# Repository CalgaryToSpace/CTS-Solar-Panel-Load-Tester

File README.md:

# CTS-Solar-Panel-Load-Tester
A solar cell/panel testing device which places a variable load on a panel to characterize its IV/PV curve

## Description

An Arduino controls a MOSFET, acting as a resistor load, to allow varying current through the MOSFET from the solar panels. Two measures are used to monitor current - an INA219 current sensor, and a shunt resistor with an op-amp network. An ADC measures the total cell/panel voltage.

The Arduino logs the voltage/current values over UART to a computer.

## Notes

* R_shunt = Full Scale Voltage / Max Expected Load Current =  40mV / 0.5A = 80mOhms, so 0.1 ohms is reasonable

## License

The software is licensed under [The Unlicense](https://choosealicense.com/licenses/unlicense/). The hardware is licensed under the [CERN Open Hardware Licence Version 2 - Permissive](https://choosealicense.com/licenses/cern-ohl-p-2.0/).

Please see the respective license documents in each sub-folder.

## Similar Projects

* **Main Reference:** https://circuitdigest.com/microcontroller-projects/adustable-electronic-dc-load-using-arduino

* https://jasper.sikken.nl/electronicload/index.html
    * Uses an [IRLZ44Z MOSFET](https://www.infineon.com/dgdl/irlz44zpbf.pdf?fileId=5546d462533600a4015356722836272a)
    * Archived on [the Wayback Machine](https://web.archive.org/web/20240229184606/https://jasper.sikken.nl/electronicload/index.html)
    
## Future Changes

* **Detect cracks in cells:** Add a MOSFET to briefly pulse a voltage across the cells and trigger an infrared camera to take a photo.

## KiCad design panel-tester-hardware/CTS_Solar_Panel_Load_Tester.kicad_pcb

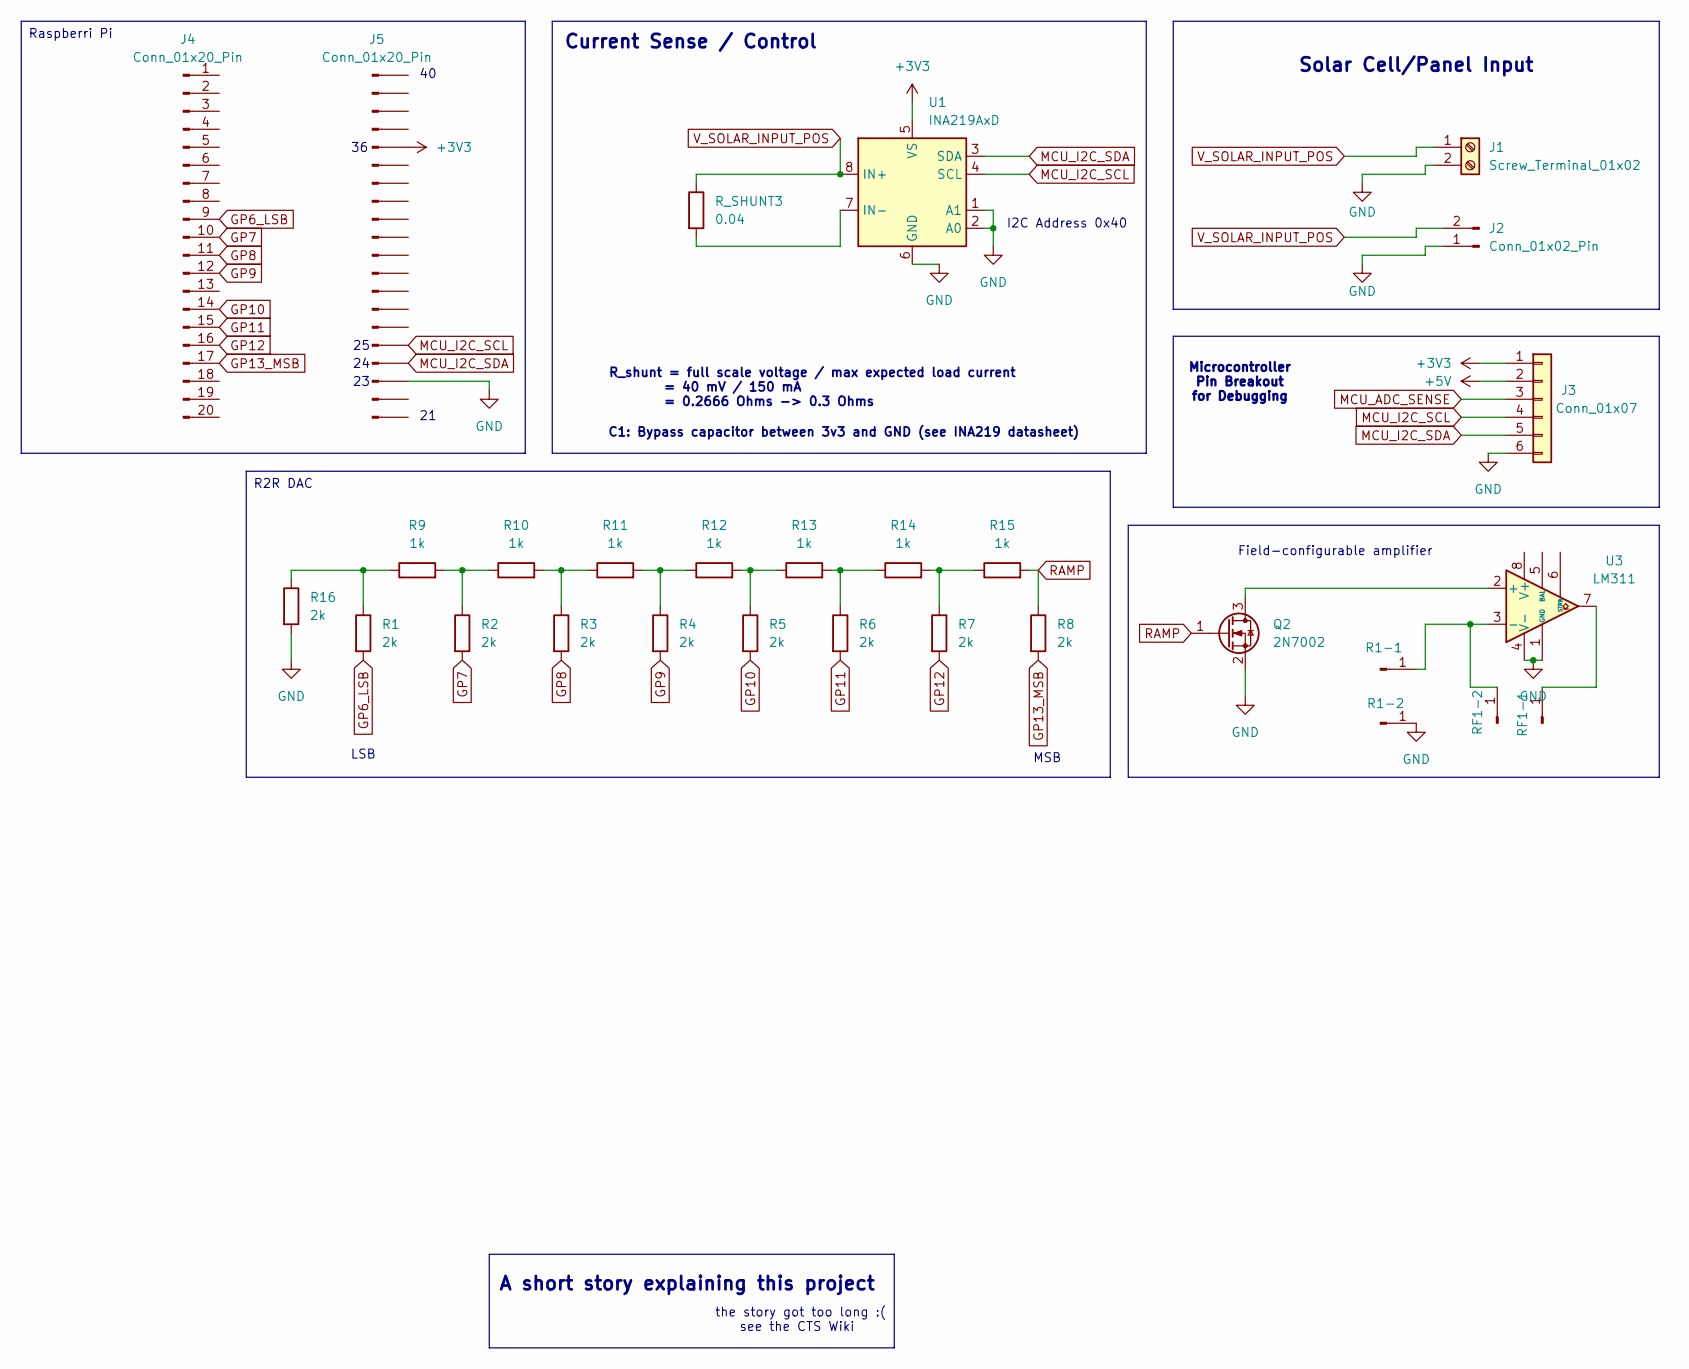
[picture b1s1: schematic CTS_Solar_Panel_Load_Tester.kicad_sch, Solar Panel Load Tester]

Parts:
J1: Screw_Terminal_01x02; TerminalBlock_bornier-2_P5.08mm
J2: Conn_01x02_Pin; PinHeader_1x02_P2.54mm_Vertical
J3: Conn_01x07; PinHeader_1x06_P2.54mm_Vertical
J4, J5: Conn_01x20_Pin; PinHeader_1x20_P2.54mm_Vertical
Q2: 2N7002; SOT-23
R1, R2, R3, R4, R5, R6, R7, R8, R16: 2k; R_1206_3216Metric_Pad1.30x1.75mm_HandSolder
R1-1, R1-2: PinHeader_1x01_P2.54mm_Vertical
R9, R10, R11, R12, R13, R14, R15: 1k; R_1206_3216Metric_Pad1.30x1.75mm_HandSolder
RF1-1, RF1-2: PinHeader_1x01_P2.54mm_Vertical
R_SHUNT3: 0.04; R_2512_6332Metric_Pad1.40x3.35mm_HandSolder
U1: INA219AxD; SOIC-8_3.9x4.9mm_P1.27mm
U3: LM311; SOIC-8-1EP_3.9x4.9mm_P1.27mm_EP2.95x4.9mm_Mask2.71x3.4mm

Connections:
+3V3: J3.1, J5.5, U1.5 (VS)
+5V: J3.2
GND: J1.2, J2.1, J3.6, J5.18, Q2.2 (S), R1-2.1, R16.2, U1.1 (A1), U1.2 (A0), U1.6 (GND), U3.1 (GND), U3.4 (V-)
GP6_LSB: J4.9, R1.2
GP7: J4.10, R2.2
GP8: J4.11, R3.2
GP9: J4.12, R4.2
GP10: J4.14, R5.2
GP11: J4.15, R6.2
GP12: J4.16, R7.2
GP13_MSB: J4.17, R8.2
MCU_ADC_SENSE: J3.3
MCU_I2C_SCL: J3.4, J5.16, U1.4 (SCL)
MCU_I2C_SDA: J3.5, J5.17, U1.3 (SDA)
unnamed: Q2.3 (D), U3.2 (+)
unnamed: R1-1.1, RF1-2.1, U3.3 (-)
unnamed: R1.1, R9.1, R16.1
unnamed: R2.1, R9.2, R10.1
unnamed: R3.1, R10.2, R11.1
unnamed: R4.1, R11.2, R12.1
unnamed: R5.1, R12.2, R13.1
unnamed: R6.1, R13.2, R14.1
unnamed: R7.1, R14.2, R15.1
unnamed: RF1-1.1, U3.7
unnamed: R_SHUNT3.2, U1.7 (IN-)
RAMP: Q2.1 (G), R8.1, R15.2
V_SOLAR_INPUT_POS: J1.1, J2.2, R_SHUNT3.1, U1.8 (IN+)

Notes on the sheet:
Current Sense / Control
Solar Cell/Panel Input
C1: Bypass capacitor between 3v3 and GND (see INA219 datasheet)
R_shunt = full scale voltage / max expected load current = 40 mV / 150 mA = 0.2666 Ohms -> 0.3 Ohms
Field-configurable amplifier
I2C Address 0x40
Microcontroller Pin Breakout for Debugging
LSB
the story got too long :( see the CTS Wiki
A short story explaining this project
MSB
R2R DAC
Raspberri Pi

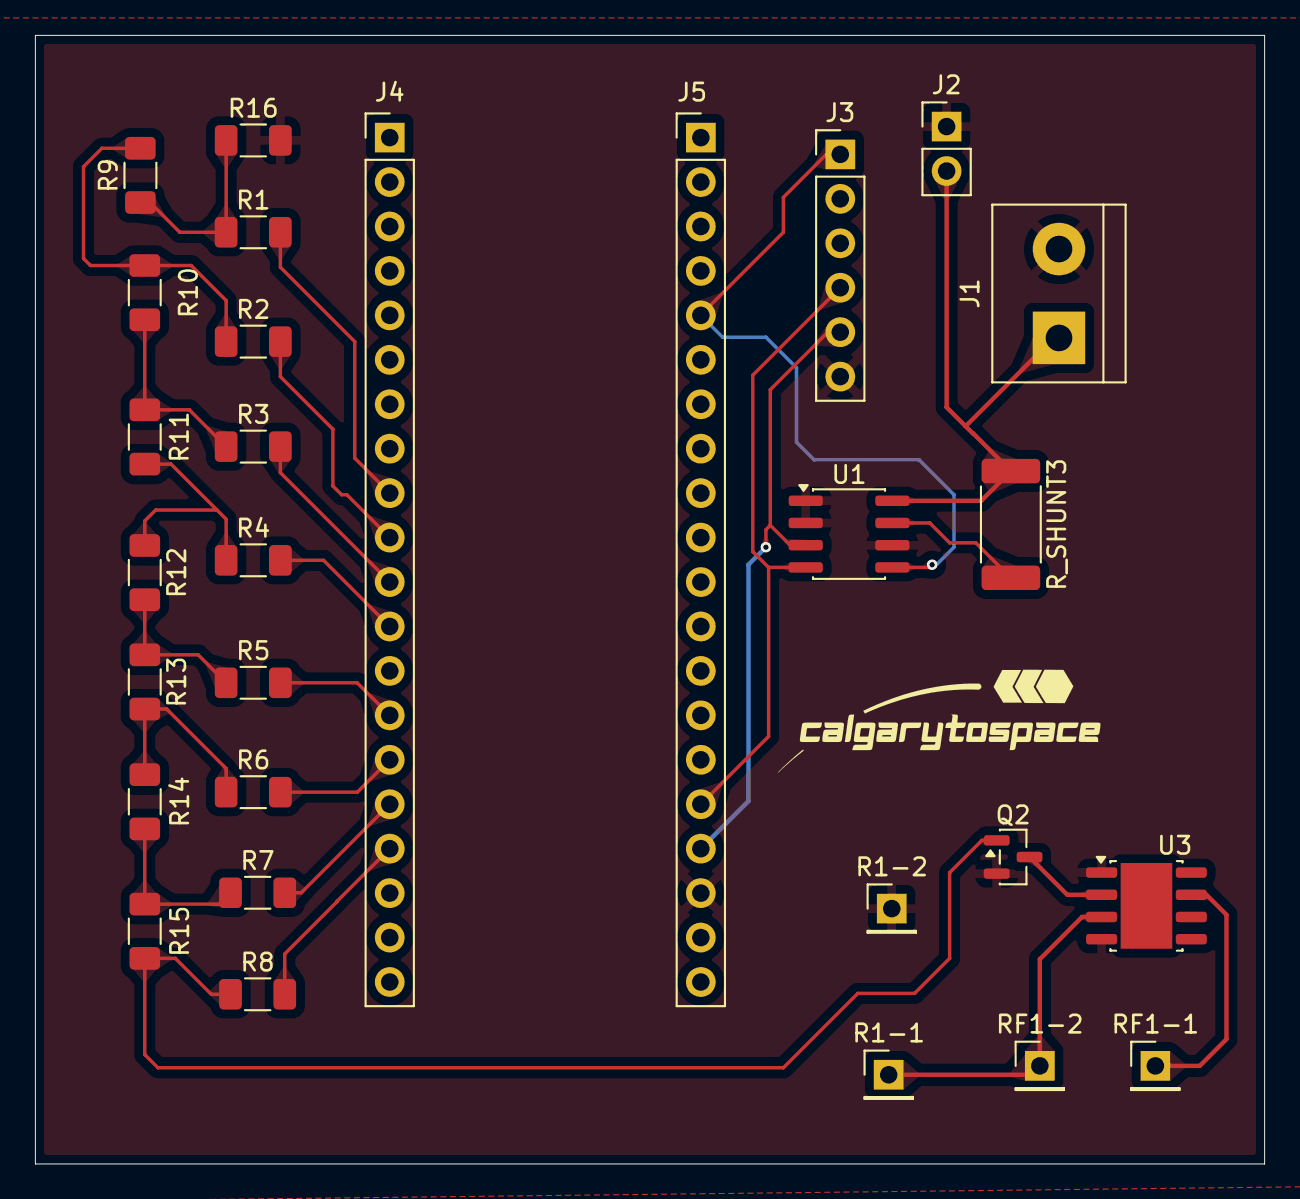
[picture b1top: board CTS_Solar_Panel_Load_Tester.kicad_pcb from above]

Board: 2 copper layers, 70.2 x 64.5 mm, 29 parts (0 on the bottom side), 25 nets.

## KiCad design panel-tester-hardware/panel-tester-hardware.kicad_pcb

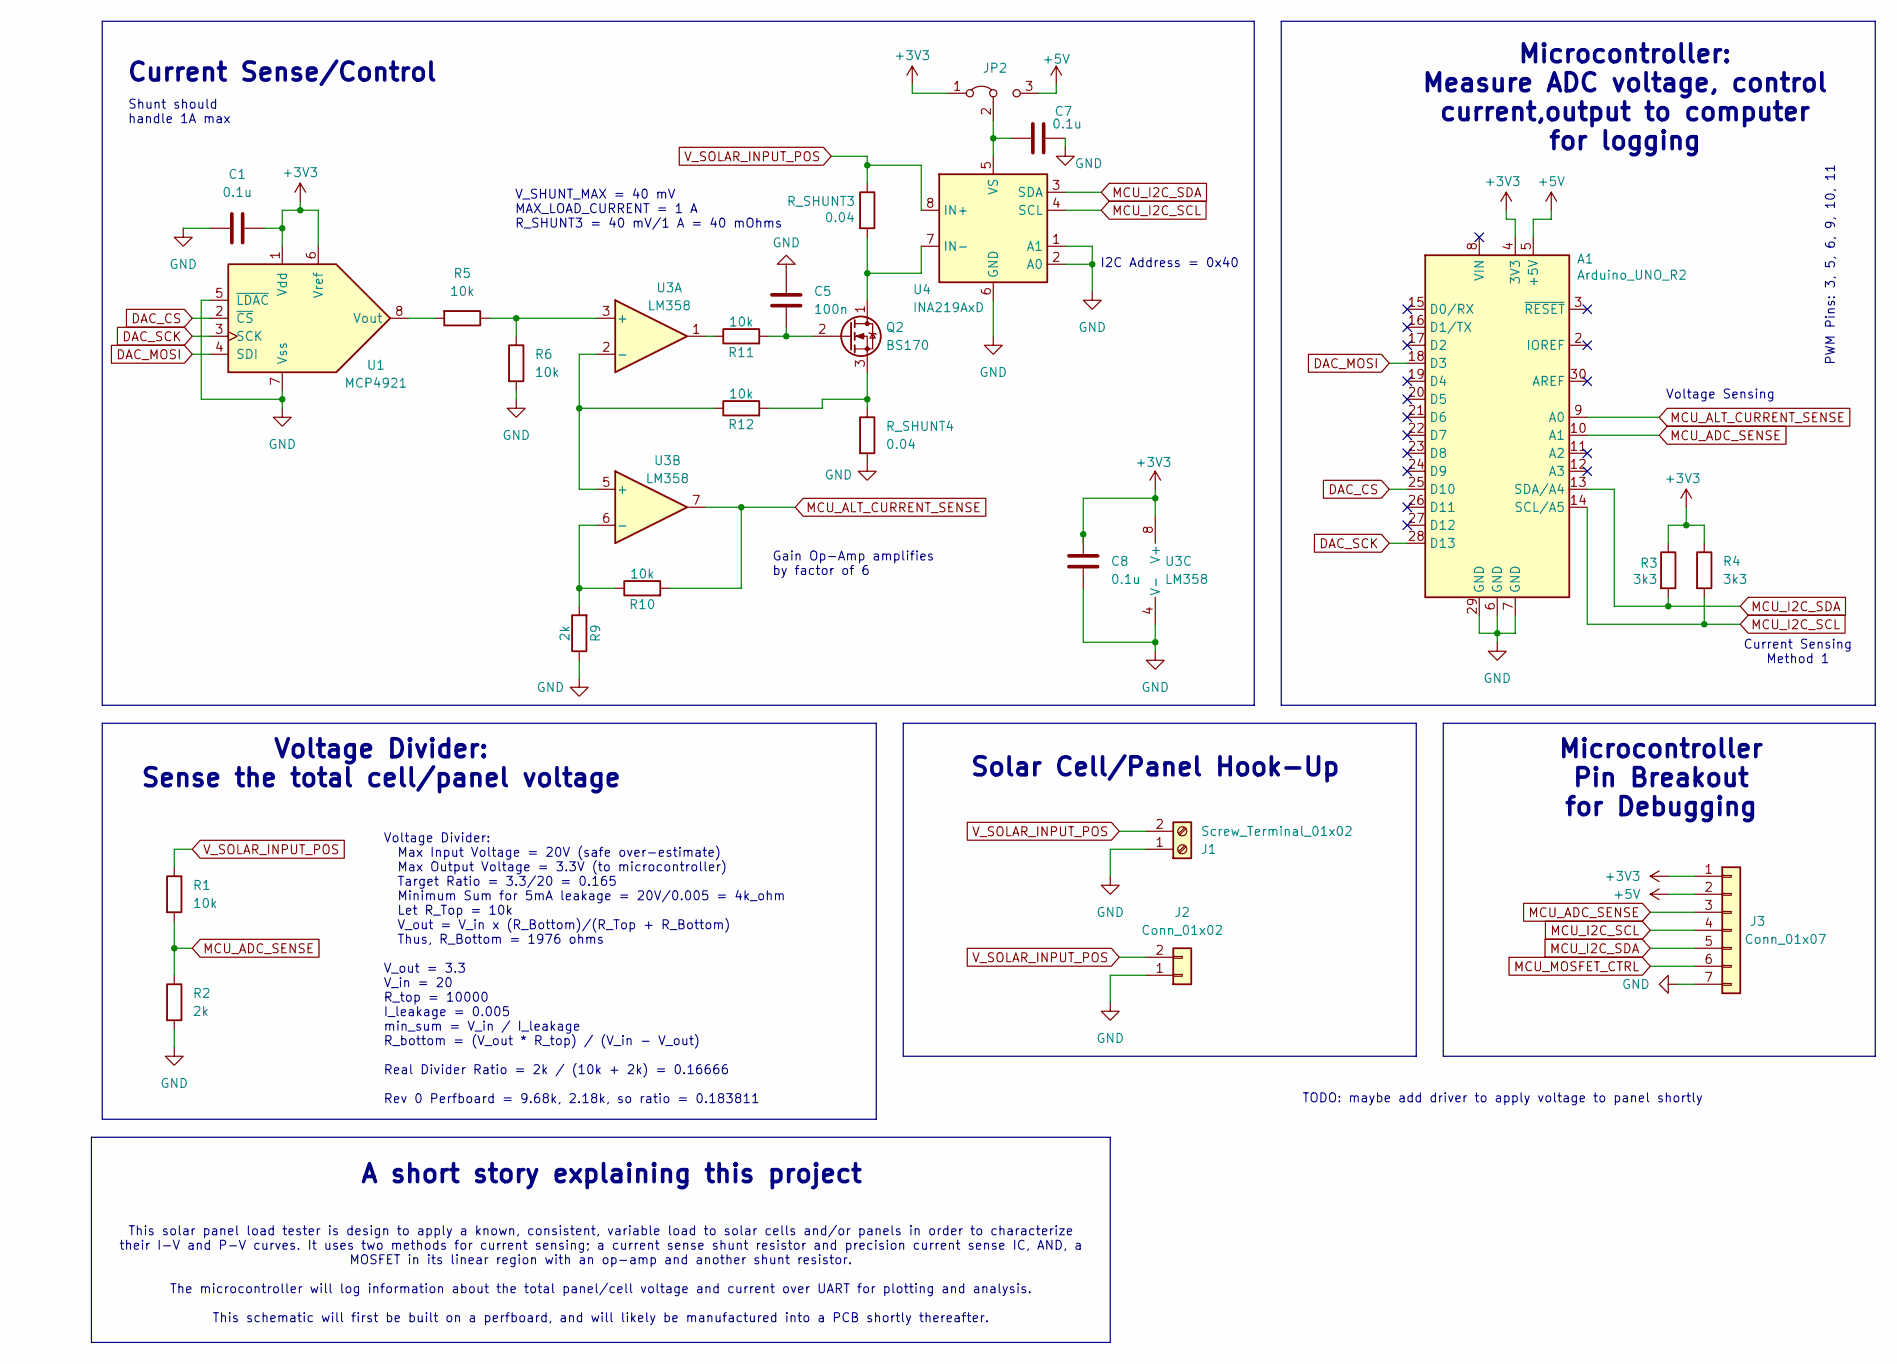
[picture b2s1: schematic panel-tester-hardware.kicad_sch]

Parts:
A1: Arduino_UNO_R2
C1, C7, C8: 0.1u; C_1206_3216Metric_Pad1.33x1.80mm_HandSolder
C5: 100n; C_1206_3216Metric_Pad1.33x1.80mm_HandSolder
J1: Screw_Terminal_01x02; TerminalBlock_bornier-2_P5.08mm
J2: Conn_01x02; PinHeader_1x02_P2.54mm_Vertical
J3: Conn_01x07; PinHeader_1x07_P2.54mm_Vertical
JP2: Jumper_3_Bridged12; SolderJumper-3_P1.3mm_Open_RoundedPad1.0x1.5mm_NumberLabels
Q2: BS170; TO-220-3_Vertical
R1, R5, R6, R10, R11, R12: 10k; R_1206_3216Metric_Pad1.30x1.75mm_HandSolder
R2, R9: 2k; R_1206_3216Metric_Pad1.30x1.75mm_HandSolder
R3, R4: 3k3; R_1206_3216Metric_Pad1.30x1.75mm_HandSolder
R_SHUNT3, R_SHUNT4: 0.04; R_2512_6332Metric_Pad1.40x3.35mm_HandSolder; LCSC C2904248
U1: MCP4921; SOIC-8_3.9x4.9mm_P1.27mm; LCSC C43499
U3: LM358; DIP-8_W7.62mm_LongPads; LCSC C18164495
U4: INA219AxD; SOIC-8_3.9x4.9mm_P1.27mm; LCSC C2155799

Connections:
+3V3: A1.4 (3V3), C1.2, C8.1, J3.1, JP2.1 (A), R3.1, R4.1, U1.1 (Vdd), U1.6 (Vref), U3.8 (V+)
+5V: A1.5 (+5V), J3.2, JP2.3 (B)
DAC_CS: A1.25 (D10), U1.2 (~CS)
DAC_MOSI: A1.18 (D3), U1.4 (SDI)
DAC_SCK: A1.28 (D13), U1.3 (SCK)
GND: A1.6 (GND), A1.7 (GND), A1.29 (GND), C1.1, C5.1, C7.2, C8.2, J1.1, J2.1, J3.7, R2.2, R6.2, R9.1, R_SHUNT4.2, U1.5 (~LDAC), U1.7 (Vss), U3.4 (V-), U4.1 (A1), U4.2 (A0), U4.6 (GND)
MCU_ADC_SENSE: A1.10 (A1), J3.3, R1.2, R2.1
MCU_ALT_CURRENT_SENSE: A1.9 (A0), R10.2, U3.7
MCU_I2C_SCL: A1.14 (SCL/A5), J3.4, R4.2, U4.4 (SCL)
MCU_I2C_SDA: A1.13 (SDA/A4), J3.5, R3.2, U4.3 (SDA)
unnamed: C7.1, JP2.2 (C), U4.5 (VS)
unnamed: Q2.1 (D), R_SHUNT3.2, U4.7 (IN-)
unnamed: C5.2, Q2.2 (G), R11.2
unnamed: Q2.3 (S), R12.2, R_SHUNT4.1
unnamed: R11.1, U3.1
unnamed: R5.1, R6.1, U3.3 (+)
unnamed: R12.1, U3.2 (-), U3.5 (+)
unnamed: R9.2, R10.1, U3.6 (-)
V_SOLAR_INPUT_POS: J1.2, J2.2, R1.1, R_SHUNT3.1, U4.8 (IN+)

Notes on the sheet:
A short story explaining this project
I2C Address = 0x40
Microcontroller Pin Breakout for Debugging
Current Sense/Control
Current Sensing Method 1
TODO: maybe add driver to apply voltage to panel shortly
Microcontroller: Measure ADC voltage, control current,output to computer for logging
Voltage Divider: Sense the total cell/panel voltage
Shunt should handle 1A max
PWM Pins: 3, 5, 6, 9, 10, 11
Voltage Sensing
V_SHUNT_MAX = 40 mV MAX_LOAD_CURRENT = 1 A R_SHUNT3 = 40 mV/1 A = 40 mOhms
Gain Op-Amp amplifies by factor of 6
Voltage Divider: Max Input Voltage = 20V (safe over-estimate) Max Output Voltage = 3.3V (to microcontroller) Target Ratio = 3.3/20 = 0.165 Minimum Sum for 5mA leakage = 20V/0.005 = 4k_ohm Let R_Top = 10k V_out = V_in x (R_Bottom)/(R_Top + R_Bottom) Thus, R_Bottom = 1976 ohms V_out = 3.3 V_in = 20 R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
Solar Cell/Panel Hook-Up
This solar panel load tester is design to apply a known, consistent, variable load to solar cells and/or panels in order to characterize their I-V and P-V curves. It uses two methods for current sensing; a current sense shunt resistor and precision current sense IC, AND, a MOSFET in its linear regi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

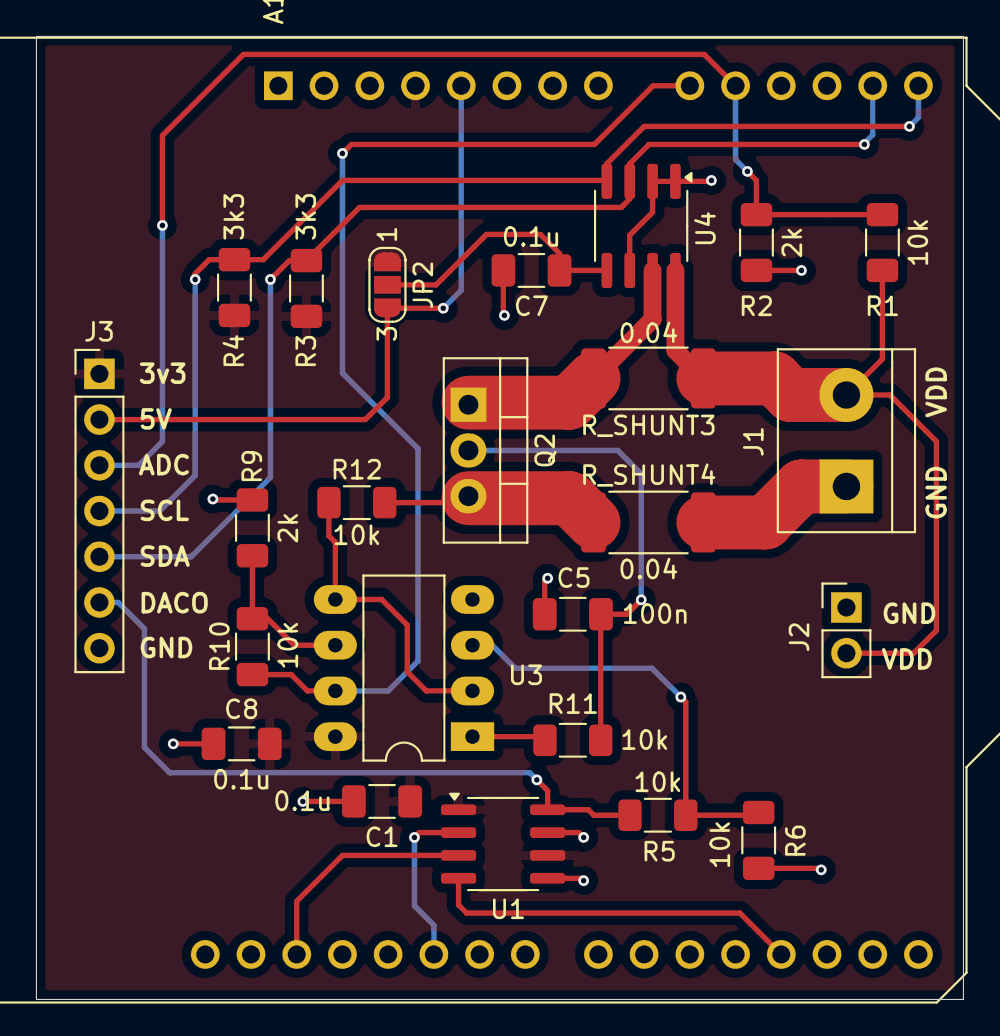
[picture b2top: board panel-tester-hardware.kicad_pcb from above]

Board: 2 copper layers, 51.5 x 53.5 mm, 25 parts (0 on the bottom side), 20 nets.

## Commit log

2024-03-15 Setup repo structure
2024-03-15 Add hardware schematic design
2024-03-16 Create platform.io structure
2024-03-16 test for variable load
2024-03-16 Convert to tabs
2024-03-16 Implement main monitoring system
2024-03-16 Add related projects to README
2024-03-27 created csv files for each cell and solar panel
2024-04-27 Changed Schematic Files
    Modified Load Testing Schematic to use two current sensing mechanisms - (1) is the existing current sensing IC, MOSFET and shunt resistor and (2) is the new op-amp mechanism with the MOSFET and shunt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
2024-05-04 Did a lot of things
    Created board layout and completed routing
2024-05-04 Created production files
    Created production files
2024-05-08 Made final slikscreen changes
2024-05-08 Created schematic PDF
2024-05-18 Updated schematic with DAC
    Added MCP4921 for analog signal creation from Arduino PWM into the input of the Op-Amp.
2024-05-18 Assigned footprints for DAC and additional passives
2024-05-18 Completed routing and aesthetic fixes
2024-05-18 Created production files
2024-06-05 Began setup and initialization of load tester firmware
2024-06-08 Add renders to README, update schematic PDF with rev number
2024-06-08 Conducted initial tests with setup code with the MCP4921 DAC
2024-06-15 Flashed initial firmware
2024-07-06 Updated main.cpp
    Attempted to isolate and debug DAC
2024-08-03 Labeled HW SPI MCP call and .begin method. Imports SPI.h instead of Wire.h
2024-08-19 Fix typos on schematic
2024-08-28 cleaned up unused variables, added note on output voltage scaling factor
2024-11-06 Initialized INA219 sensor, created functions for voltage loop and INA219 measurements
2024-11-30 Added INA219 Testing firmware, moved code for voltage_loop function into a main function
2024-12-18 Firmware: support PCB Rev 2
2025-02-05 Add files via upload
    Version 2 Schematic
2025-02-17 deleted new_main
2025-02-20 Fix potentiometer schematic and import custom footprint
2025-02-22 added code for INA219 for stm
2025-02-25 Add microcontroller breakout pins, update potentiometer footprint
2025-02-25 PCB layout v1
2025-02-25 Add 3D model
2025-02-25 Add footprint file
2025-02-26 Add bluepill footprint
2025-02-26 Bluepill layout edits
2025-02-26 Revert "Bluepill layout edits"
    This reverts commit 7404dadbf005f9dc7929b7ea0254307db19fd9e4.
2025-02-26 Revert "Add bluepill footprint"
    This reverts commit 3df0fce7c146b90b9d7b39e29235daf38b6f8407.
2025-02-26 Bluepill footprint & layout
2025-02-26 Bluepill files
2025-02-26 Import bluepill symbols
2025-02-26 Rename potentiometer footprint
2025-02-26 ERC/DRC fixes
2025-03-01 Random changes to rev 2, before big changes
2025-03-02 Schematic fixes + UART breakout header
    TODO: Confirm R_shunt value
2025-03-03 Layout fixes, add mounting holes, silkscreen edits
    TODO: Add bypass capacitor & reroute, use thicker trace for high current path
2025-03-03 Add bypass capacitor
2025-03-03 Routing
2025-03-03 1.5 mm net class for solar panel input path
2025-03-06 Add 1 mm net class for high current path
2025-03-08 Add micropython INA code for other system
2025-03-08 Add ADC reader
2025-03-21 Tiny fixes
2025-03-28 firmware: Enable LED
2025-05-17 Created Solar Panel LT Spice Sim
    Not finished, has variable current source to represent varied illumination with voltage source purely being a value for illumination. R1 represents leakage and R2 represents internal resistance. Need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
2025-10-17 cleaned and reversed polarity of solar panel
2025-10-18 data
2025-10-18 added excel sheet
2025-10-18 create solar cell symbol
2025-10-19 cytkhtgl
2025-10-29 variable resistor test
2025-11-15 circuit simulation modification
2025-11-26 made schematic for the amplifier and MOSFET
2025-11-29 fixed footprints and added headers
2026-01-10 R2R DAC added
2026-01-10 added DAC
2026-01-17 PCB passes DRC
2026-01-17 checklist almost done
2026-01-21 PCB is good
2026-01-21 added raspberrypi files
2026-01-21 added busio import
2026-02-07 latest
2026-03-04 changed solar panel connection
2026-03-11 added the good code files
2026-03-25 added dac graphs and things
